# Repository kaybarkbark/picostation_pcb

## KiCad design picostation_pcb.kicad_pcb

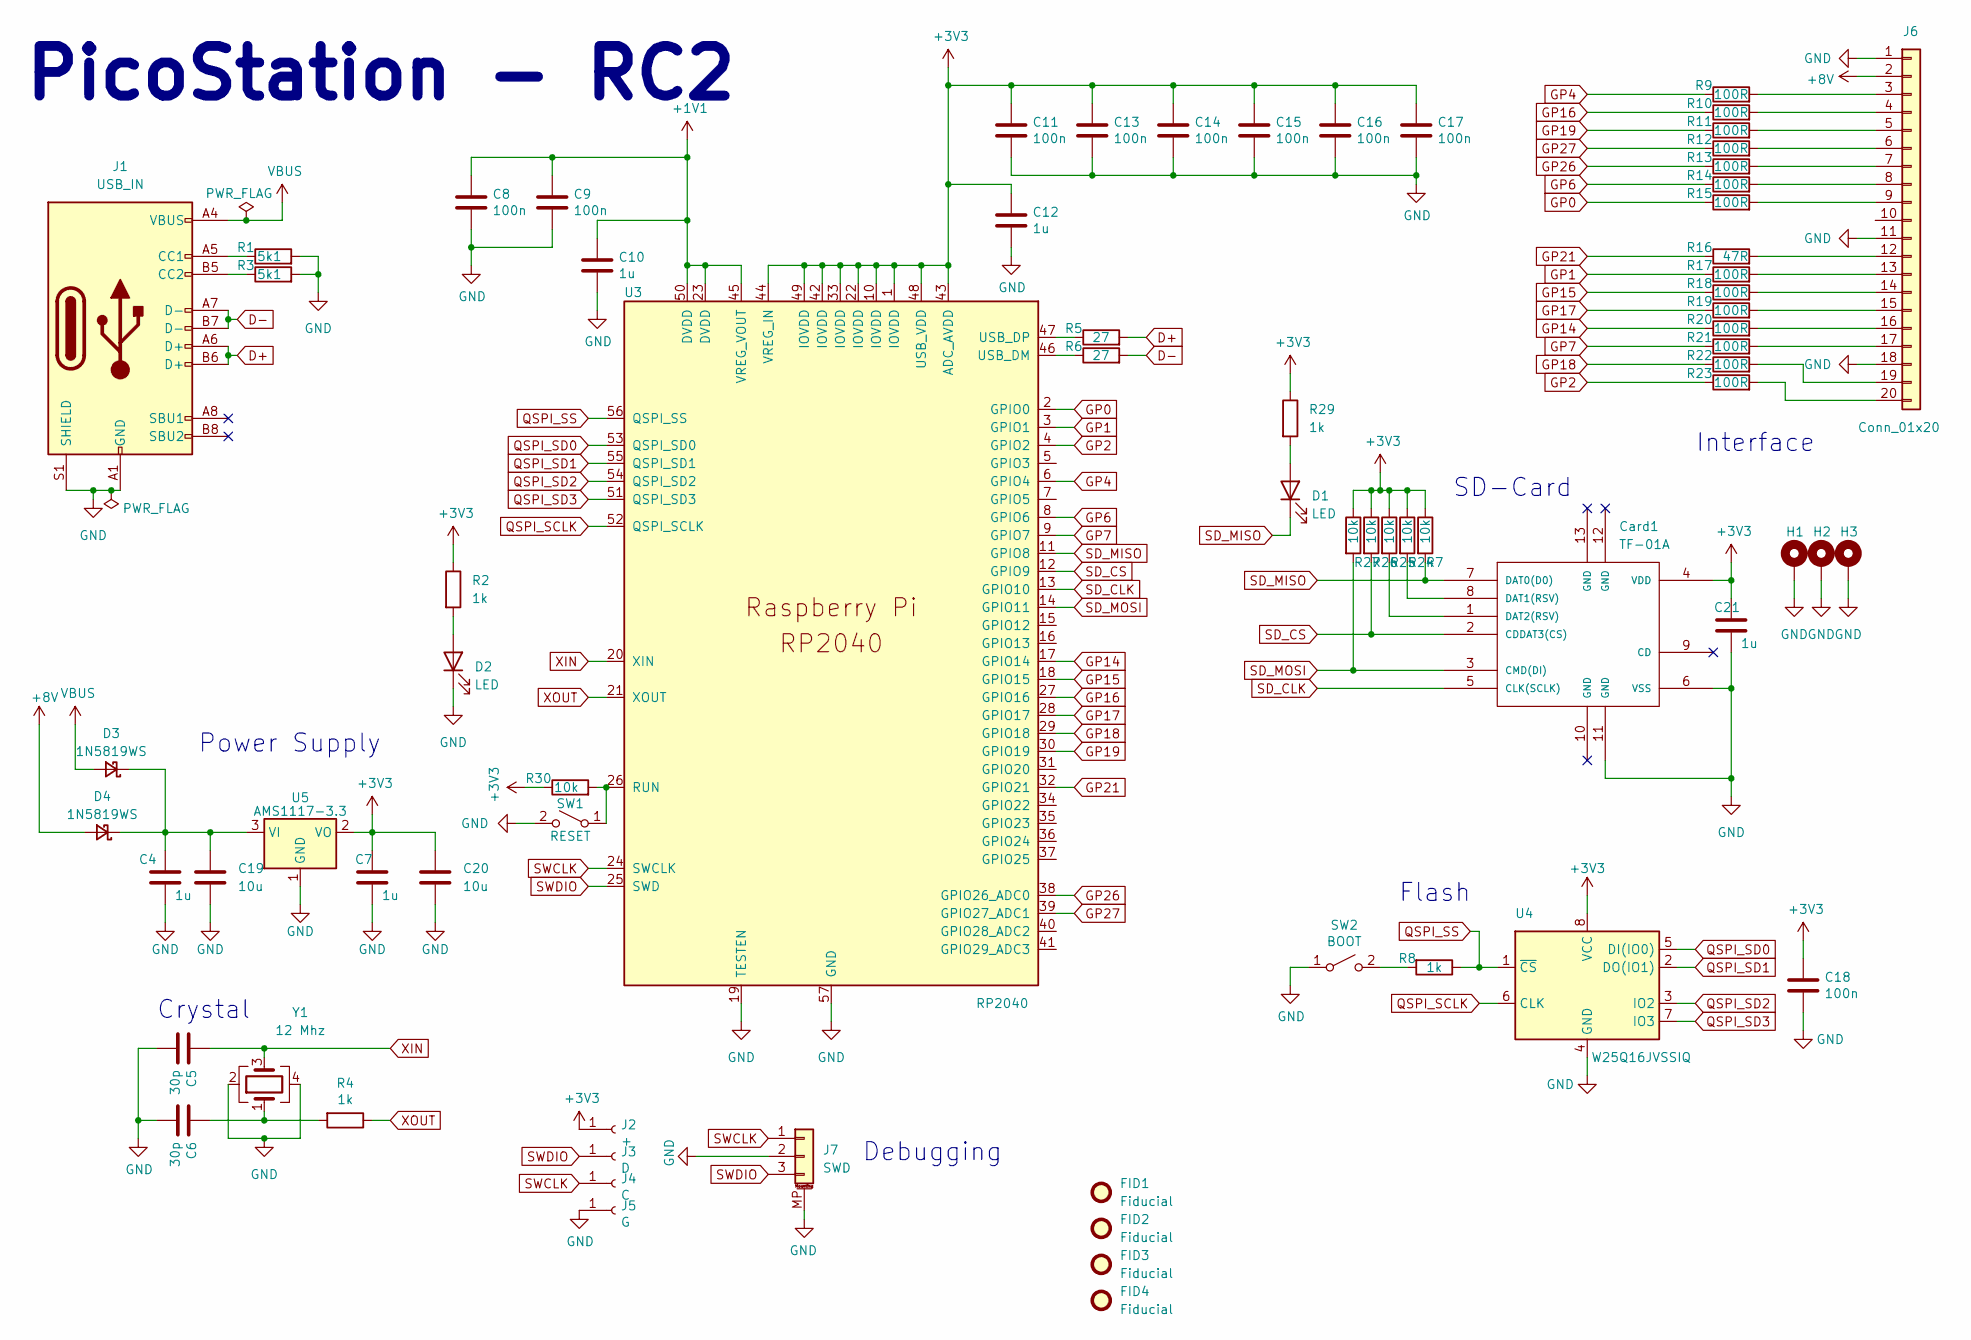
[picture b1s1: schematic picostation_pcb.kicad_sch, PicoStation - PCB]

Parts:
C4, C7, C10, C12, C21: 1u; C_0603_1608Metric_Pad1.08x0.95mm_HandSolder; LCSC C52923
C5, C6: 30p; C_0603_1608Metric_Pad1.08x0.95mm_HandSolder; LCSC C1570
C8, C9, C11, C13, C14, C15, C16, C17, C18: 100n; C_0603_1608Metric_Pad1.08x0.95mm_HandSolder; LCSC C1525
C19, C20: 10u; C_0805_2012Metric_Pad1.18x1.45mm_HandSolder; LCSC C15850
Card1: TF-01A; TF-SMD_TF-01A; LCSC C91145
D1, D2: LED; LED_0805_2012Metric_Pad1.15x1.40mm_HandSolder
D3, D4: 1N5819WS; D_SOD-323; LCSC C191023
FID1, FID2, FID3, FID4: Fiducial; Fiducial_1mm_Mask2mm
H1, H2, H3: MountingHole_2.2mm_M2_DIN965_Pad
J1: USB_IN; USB_C_Receptacle_HRO_TYPE-C-31-M-12; LCSC C2765186
J2: +; TestPoint_Pad_D1.5mm
J3: D; TestPoint_Pad_D1.5mm
J4: C; TestPoint_Pad_D1.5mm
J5: G; TestPoint_Pad_D1.5mm
J6: Conn_01x20; Molex_200528-0200_1x20-1MP_P1.00mm_Horizontal
J7: SWD; JST_SH_BM03B-SRSS-TB_1x03-1MP_P1.00mm_Vertical
R1, R3: 5k1; R_0603_1608Metric_Pad0.98x0.95mm_HandSolder
R2, R29: 1k; R_0603_1608Metric_Pad0.98x0.95mm_HandSolder
R4, R8: 1k; R_0603_1608Metric_Pad0.98x0.95mm_HandSolder; LCSC C11702
R5, R6: 27; R_0603_1608Metric_Pad0.98x0.95mm_HandSolder
R7, R24, R25, R26, R27, R30: 10k; R_0603_1608Metric_Pad0.98x0.95mm_HandSolder
R9, R10, R11, R12, R13, R14, R15, R17, R18, R19, R20, R21, R22, R23: 100R; R_0603_1608Metric_Pad0.98x0.95mm_HandSolder
R16: 47R; R_0603_1608Metric_Pad0.98x0.95mm_HandSolder
SW1: RESET; SW_SPST_EVPBF
SW2: BOOT; SW_SPST_EVPBF
U3: RP2040; RP2040-QFN-56; LCSC C2040
U4: W25Q16JVSSIQ; SOIC-8_5.23x5.23mm_P1.27mm; LCSC C131025
U5: AMS1117-3.3; SOT-223-3_TabPin2; LCSC C6186
Y1: 12 Mhz; Crystal_SMD_3225-4Pin_3.2x2.5mm; LCSC C9002

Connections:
+1V1: C8.1, C9.1, C10.1, U3.23 (DVDD), U3.45 (VREG_VOUT), U3.50 (DVDD)
+3V3: C7.1, C11.1, C12.1, C13.1, C14.1, C15.1, C16.1, C17.1, C18.1, C20.1, C21.1, Card1.4 (VDD), J2.1, R2.1, R7.1, R24.1, R25.1, R26.1, R27.1, R29.1, R30.1, U3.1 (IOVDD), U3.10 (IOVDD), U3.22 (IOVDD), U3.33 (IOVDD), U3.42 (IOVDD), U3.43 (ADC_AVDD), U3.44 (VREG_IN), U3.48 (USB_VDD), U3.49 (IOVDD), U4.8 (VCC), U5.2 (VO)
+8V: D4.2 (A), J6.2
D+: J1.A6 (D+), J1.B6 (D+), R5.2
D-: J1.A7 (D-), J1.B7 (D-), R6.2
GND: C4.2, C5.2, C6.2, C7.2, C8.2, C9.2, C10.2, C11.2, C12.2, C13.2, C14.2, C15.2, C16.2, C17.2, C18.2, C19.2, C20.2, C21.2, Card1.6 (VSS), Card1.11 (GND), D2.1 (K), H1.1, H2.1, H3.1, J1.A1 (GND), J1.A12 (GND), J1.B1 (GND), J1.B12 (GND), J1.S1 (SHIELD), J5.1, J6.1, J6.11, J6.18, J7.2, J7.MP (MountPin), R1.2, R3.2, SW1.2 (B), SW2.1 (A), U3.19 (TESTEN), U3.57 (GND), U4.4 (GND), U5.1 (GND), Y1.2, Y1.4
GP0: R15.1, U3.2 (GPIO0)
GP1: R17.1, U3.3 (GPIO1)
GP2: R23.1, U3.4 (GPIO2)
GP4: R9.1, U3.6 (GPIO4)
GP6: R14.1, U3.8 (GPIO6)
GP7: R21.1, U3.9 (GPIO7)
GP14: R20.1, U3.17 (GPIO14)
GP15: R18.1, U3.18 (GPIO15)
GP16: R10.1, U3.27 (GPIO16)
GP17: R19.1, U3.28 (GPIO17)
GP18: R22.1, U3.29 (GPIO18)
GP19: R11.1, U3.30 (GPIO19)
GP21: R16.1, U3.32 (GPIO21)
GP26: R13.1, U3.38 (GPIO26_ADC0)
GP27: R12.1, U3.39 (GPIO27_ADC1)
unnamed: C6.1, R4.2, Y1.1
unnamed: Card1.8 (DAT1(RSV)), R24.2
unnamed: Card1.1 (DAT2(RSV)), R25.2
unnamed: D1.2 (A), R29.2
unnamed: D2.2 (A), R2.2
unnamed: C4.1, C19.1, D3.1 (K), D4.1 (K), U5.3 (VI)
unnamed: J1.A5 (CC1), R1.1
unnamed: J1.B5 (CC2), R3.1
unnamed: J6.3, R9.2
unnamed: J6.4, R10.2
unnamed: J6.5, R11.2
unnamed: J6.6, R12.2
unnamed: J6.7, R13.2
unnamed: J6.8, R14.2
unnamed: J6.9, R15.2
unnamed: J6.12, R16.2
unnamed: J6.13, R17.2
unnamed: J6.14, R18.2
unnamed: J6.15, R19.2
unnamed: J6.16, R20.2
unnamed: J6.17, R21.2
unnamed: J6.19, R22.2
unnamed: J6.20, R23.2
unnamed: R30.2, SW1.1 (A), U3.26 (RUN)
unnamed: R8.2, SW2.2 (B)
unnamed: R6.1, U3.46 (USB_DM)
unnamed: R5.1, U3.47 (USB_DP)
QSPI_SCLK: U3.52 (QSPI_SCLK), U4.6 (CLK)
QSPI_SD0: U3.53 (QSPI_SD0), U4.5 (DI(IO0))
QSPI_SD1: U3.55 (QSPI_SD1), U4.2 (DO(IO1))
QSPI_SD2: U3.54 (QSPI_SD2), U4.3 (IO2)
QSPI_SD3: U3.51 (QSPI_SD3), U4.7 (IO3)
QSPI_SS: R8.1, U3.56 (QSPI_SS), U4.1 (~CS)
SD_CLK: Card1.5 (CLK(SCLK)), U3.13 (GPIO10)
SD_CS: Card1.2 (CDDAT3(CS)), R26.2, U3.12 (GPIO9)
SD_MISO: Card1.7 (DAT0(D0)), D1.1 (K), R7.2, U3.11 (GPIO8)
SD_MOSI: Card1.3 (CMD(DI)), R27.2, U3.14 (GPIO11)
SWCLK: J4.1, J7.1, U3.24 (SWCLK)
SWDIO: J3.1, J7.3, U3.25 (SWD)
VBUS: D3.2 (A), J1.A4 (VBUS), J1.A9 (VBUS), J1.B4 (VBUS), J1.B9 (VBUS)
XIN: C5.1, U3.20 (XIN), Y1.3
XOUT: R4.1, U3.21 (XOUT)

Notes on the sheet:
SD-Card
Flash
Debugging
Interface
Crystal
Power Supply
PicoStation - RC2

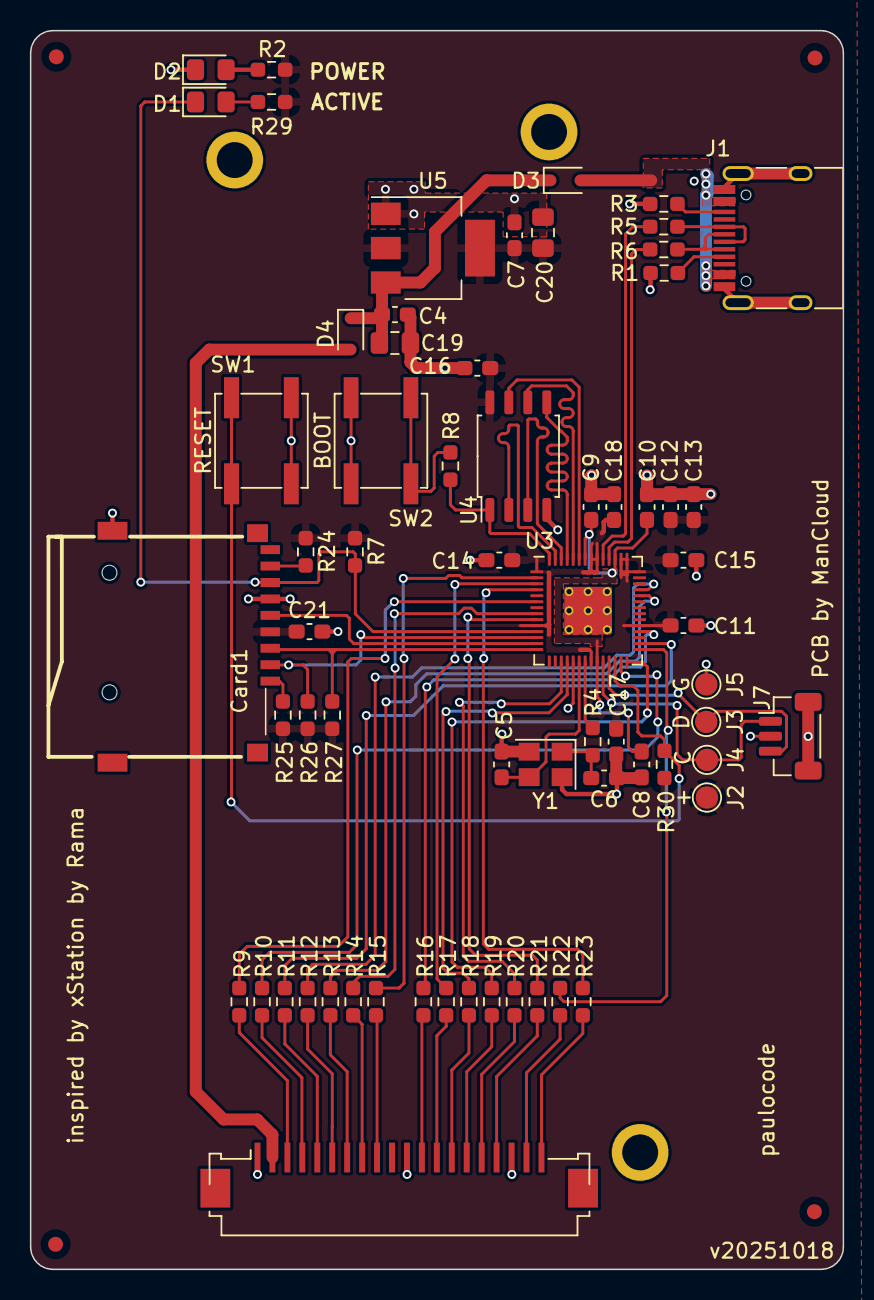
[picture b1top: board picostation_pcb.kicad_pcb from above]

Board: 2 copper layers, 54.4 x 82.9 mm, 72 parts (0 on the bottom side), 63 nets.

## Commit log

2025-10-18 Small PCB Improvements
    - Remove 5V 7805 regulator, diode OR the power from the 8V line into the
    AMS1117-3v3 instead
    - Add a debug header that is compatible with the Raspberry Pi Debug
    Probe
    - Add a reset switch
2025-10-18 Small PCB Improvements
    Ordered a fully assembled board from JLCPCB, tested it for 5+ hours
    while playing the fan translation of Policenauts. Tested several
    other games as well for a short period of time (Silent Hill, Crash
    Bandicoot, Spyro)
    - Remove 5V 7805 regulator, diode OR the power from the 8V line into the
    AMS1117-3v3 instead (this part can accept up to 18V)
